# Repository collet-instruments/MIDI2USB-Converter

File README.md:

# 🎹 MIDI2USB Converter

<p align="center">

</p>

<p align="center">
  <strong>STM32F401-based USB MIDI converter supporting both MIDI 1.0 and MIDI 2.0 protocols.</strong>
</p>

## ✨ Features
- 🎵 **Dual Protocol Support**: MIDI 1.0 and MIDI 2.0 protocols
- 🔌 **USB Device Classes**: 
  - MIDI 1.0: Standard USB MIDI Class
  - MIDI 2.0: USB MIDI 2.0 Class with UMP support
- 🔄 **Dynamic Mode Switching**: Automatic detection based on SETUP switch
- 📦 **UMP (Universal MIDI Packet)**: Full support for MIDI 2.0 messaging
- 🔍 **MIDI-CI**: MIDI-CI v1.2 support
- 💡 **Visual Feedback**: LED status indicators
  - Red LED: USB MIDI 1.0 mode indicator
  - Blue LED: USB MIDI 2.0 mode indicator
- ⚡ **Real-time OS**: FreeRTOS-based multitasking
- 🔗 **UART Bridge**: Hardware TRS MIDI Type-A (3.5mm jack) interface support

## 📖 Usage

### Using USB MIDI1.0 Mode

- Switch SETUP (SW1) to MIDI1.0 and connect the USB Type-C port (J1) to a USB host
- The red LED (D5) will light up
- MIDI packets received at the MIDI IN port (J3) will be sent to the USB host
- Similarly, MIDI packets sent from the USB host will be output to the MIDI OUT port (J4)
- Data transfer status can be monitored via indicator LEDs (D2, D3) for both MIDI IN and MIDI OUT ports

### Using USB MIDI2.0 Mode

- Switch SETUP (SW1) to MIDI2.0 and connect the USB Type-C port (J1) to a USB host
- The blue LED (D6) will light up
- MIDI packets (MIDI1.0 byte stream) received at the MIDI IN port (J3) are converted to USB MIDI2.0 UMP (Universal MIDI Packet) and sent to the USB host
  - At this time, MIDI1.0 Voice Messages are extended to MIDI2.0 Protocol (UMP Message Type 4)
  - Similarly, MIDI2.0 UMP sent from the USB host is converted to MIDI1.0 byte stream and output to the MIDI OUT port (J4)
    - Since MIDI2.0 Protocol sent from the USB host is converted to MIDI1.0 Protocol, some data may be lost
- Data transfer status can be monitored via indicator LEDs (D2, D3) for both MIDI IN and MIDI OUT ports
- Some operating systems do not support USB MIDI2.0 drivers, in which case MIDI2.0 mode may not be available. Please use MIDI1.0 mode in such cases.

## 🔄 Protocol Conversion Rules

### MIDI 1.0 → MIDI 2.0 Conversion
The converter performs a 2-stage conversion process:
1. **Stage 1**: MIDI 1.0 byte stream → UMP (MIDI 1.0 Protocol)
2. **Stage 2**: UMP (MIDI 1.0 Protocol) → UMP (MIDI 2.0 Protocol)

**Key transformations**:
- **Resolution Enhancement**: 7-bit values are scaled up to 16-bit or 32-bit
  - Note velocity: 7-bit → 16-bit (e.g., 127 → ~65024)
  - Control Change values: 7-bit → 32-bit
  - Pitch Bend: 14-bit → 32-bit
- **Message Type**: Voice Messages are upgraded to UMP Message Type 4 (MIDI 2.0 Protocol)

### MIDI 2.0 → MIDI 1.0 Conversion
Direct conversion from UMP to MIDI 1.0 byte stream:

**Key transformations**:
- **Resolution Reduction**: High-resolution values are scaled down
  - Control values: 32-bit → 7-bit
- **Special handling for Note On velocity 0**:
  - In MIDI 2.0, Note On with velocity 0 remains a Note On
  - During conversion, velocity 0 is changed to 1 to prevent unintended Note Off behavior in MIDI 1.0
- **Data Loss**: MIDI 2.0-specific features (extended CC, per-note controllers) cannot be represented in MIDI 1.0

### Conversion Examples
- **MIDI 1.0 Note On**: `90 3C 64` (Ch1, Middle C, Velocity 100)
  → **MIDI 2.0 UMP**: `40902C00 32800000` (Velocity ≈ 51200)
  
- **MIDI 2.0 Note On**: Velocity 32768 (50% intensity)
  → **MIDI 1.0**: `90 3C 40` (Velocity 64, precision reduced)

## ⚠️ Caution

- The IN/OUT terminals of this product are **TRS MIDI Type-A only**. Do not use other types of cables.  
- Make sure not to confuse IN and OUT connections. Incorrect wiring may cause reverse current and damage your equipment.  
- This product is designed for **USB Type-C 5V power supply only**. Do not apply any other voltage.  
- The product may be damaged by static electricity. Please handle with proper ESD precautions.  
- Modifications or improper soldering may cause malfunction or accidents.  
- Do not use in environments with high temperature, high humidity, direct sunlight, or condensation.  
- Compatibility with all MIDI devices is **not guaranteed**.  

## 📜 Disclaimer

- This product is provided for **electronic hobby, educational, and research purposes**.  
- It is **not a consumer-ready product** and has **not been certified** under any safety standards or regulations (such as **PSE, Radio Act certification, CE, UL**, etc.).  
- By purchasing and using this product, you agree to the following terms:

### Use at Your Own Risk
- We accept no responsibility for any damage to equipment, personal injury, fire, data loss, or any other loss or accident resulting from the use of this product.

### Limitations of Use
- Do not use this product in industrial equipment, medical devices, safety systems, or any other applications where human life or property may be at risk.  
- Continuous long-term operation or use under heavy loads is not intended.

### Modification and Connections
- We are not responsible for any malfunction or damage caused by modification of this product or connection to unintended devices.

### Returns and Warranty
- If a manufacturing defect is confirmed, we will provide a replacement or refund.  
- No other warranties or guarantees are offered.

## ⚙️ Modification and Collaboration

- This product is provided as **open hardware**.  
  You are free to modify, reuse, or build upon the circuit and firmware.  
  However, **we cannot guarantee the operation or safety of modified versions**.  

- We welcome contributions from developers and users who wish to improve the design.  
  Please feel free to share feedback, modifications, or enhancement ideas.  

## 🛠️ Build Requirements

- ARM GCC toolchain (arm-none-eabi-gcc)
- CMake (3.22 or later)
- Ninja build system
- Git (for submodules)

## 📥 Getting Started

### Clone the Repository

```bash
git clone --recursive https://github.com/collet-instruments/MIDI2USB-Converter.git
cd MIDI2USB-Converter

# If you already cloned without --recursive, initialize submodules
git submodule init
git submodule update
```
### IDE Integration

**VS Code**: Use CMake extension for building and debugging with ST-Link.

- [STM32 VS Code extension](https://www.st.com/content/st_com/ja/campaigns/stm32-vs-code-extension-z11.html) makes setup easy.

## 🔨 Building

### Using CMake

```bash
# Configure the project
cmake --preset Debug

# Build the firmware
cmake --build --preset Debug

# The output files will be in build/Debug/
```
### Build Configurations

The project supports multiple build configurations:

- **Debug**: Development build with debug symbols (default)
- **Release**: Optimized build for production (-O2 optimization)
- **RelWithDebInfo**: Release build with debug info
- **MinSizeRel**: Size-optimized build (-Os optimization)

## 🧪 Testing

The project includes a comprehensive unit test suite using Unity framework.

### Running Tests

```bash
# Run all tests
cd test
make test

# Run specific test
make test-mode_manager

# Run tests with coverage
make clean
make COVERAGE=1
make test
```

## ✅ Code Quality

### Code Formatting

The project uses clang-format for code formatting. Configuration is in `.clang-format`.

```bash
# Format code
clang-format -i Core/Src/*.c Core/Inc/*.h

# Check formatting without modifying files
clang-format --dry-run --Werror Core/Src/*.c Core/Inc/*.h
```

### Static Analysis

```bash
# Run cppcheck
cppcheck --enable=warning,style,performance,portability \
  -I Core/Inc \
  Core/Src/
```

### CI/CD

GitHub Actions automatically runs on every push and pull request:

#### Workflows:
- **ci.yml**: Main CI pipeline
  - Builds STM32 firmware  
  - Runs all unit tests
  - Uploads firmware artifacts
  
- **code-quality.yml**: Code quality checks
  - Static analysis with cppcheck
  - Code formatting verification with clang-format
  
- **release.yml**: Automated releases
  - Triggers on version tags (v*)
  - Creates GitHub releases with firmware binaries

## 📁 Project Structure

```
├── Core/               # Application source code
├── Drivers/            # STM32 HAL and CMSIS drivers
├── submodules/         # External dependencies
│   ├── FreeRTOS-Kernel/
│   ├── tinyusb/
│   ├── AM_MIDI2.0Lib/
│   ├── tusb_ump/
│   └── Unity/
├── test/               # Unit tests (Unity framework)
│   ├── src/            # Test source files
│   ├── mock/           # Mock implementations
│   └── include/        # Test headers
├── ci/                 # CI/CD scripts
└── .github/            # CI/CD workflows
```

## 📦 Submodules

This project uses the following Git submodules:

| Submodule | Repository URL | Description |
|-----------|---------------|-------------|
| **FreeRTOS-Kernel** | https://github.com/FreeRTOS/FreeRTOS-Kernel.git | FreeRTOS kernel files only |
| **tinyusb** | https://github.com/hathach/tinyusb.git | An open source cross-platform USB stack for embedded system |
| **tusb_ump** | https://github.com/midi2-dev/tusb_ump | USB MIDI 2.0 tinyUSB Device driver with backwards compatibility to USB MIDI 1.0 |
| **AM_MIDI2.0Lib** | https://github.com/midi2-dev/AM_MIDI2.0Lib | A MIDI 2.0 C++ Library |
| **Unity** | https://github.com/ThrowTheSwitch/Unity.git | Simple unit testing for C |

## 🔧 Hardware

### 🎛️ Microcontroller
- **MCU**: STM32F401CBU6 (ARM Cortex-M4, 84MHz)
- **Flash**: 256KB
- **RAM**: 64KB

### 🔌 Interfaces
- **USB**: Full-Speed USB 2.0 (12Mbps)
- **UART**: MIDI serial interface (31.25 kbaud)
  - TX: PA2 (USART2_TX)
  - RX: PA3 (USART2_RX)
- **DEBUG**: ST-Link support (J2 connector)

### 📍 GPIO Pins
- **Mode Selection**: PA5 (SETUP pin)
  - High: USB MIDI 2.0 mode
  - Low: USB MIDI 1.0 mode
- **LEDs**:
  - M1LED: PA4 - USB MIDI 1.0 mode indicator
  - M2LED: PA6 - USB MIDI 2.0 mode indicator

### ⚡ Power
- Powered via USB (5V)
- 3.3V internal operation

## 💻 Development

### Running Tests Locally
```bash
# Quick test before pushing
./ci/test-ci-locally.sh

# Install optional CI tools
./ci/install-ci-tools.sh
```

### Debugging

1. **VS Code**: Use CMake extension and ST-Link for debugging
2. **OpenOCD**: Manual debugging with GDB

- Connect the J2 connector (NRST, SYS_SWCLK, SYS_SWDIO) to ST-Link for debugging. USART1 is also available for printf debugging.

## 🤝 Contributing

We welcome contributions! Please see [CONTRIBUTING.md](CONTRIBUTING.md) for details on:
- How to submit issues
- How to submit pull requests
- Code style guidelines
- Development setup

## 📜 Code of Conduct

This project adheres to a Code of Conduct. By participating, you are expected to uphold this code. Please see [CODE_OF_CONDUCT.md](CODE_OF_CONDUCT.md) for details.

## 📄 License

This project is licensed under the MIT License - see the [LICENSE](LICENSE) file for details.

**Hardware Design**: All hardware design files including schematics, PCB layouts, and manufacturing files in the `hardware/` directory are also covered under the same MIT License.

### Third-party Licenses

This project uses the following open-source libraries:
- **FreeRTOS-Kernel**: MIT License
- **TinyUSB**: MIT License
- **AM_MIDI2.0Lib**: MIT License
- **Unity Test Framework**: MIT License
- **STM32 HAL Drivers**: BSD 3-Clause License (STMicroelectronics)

## 👥 Authors and Acknowledgments

- USB MIDI 2.0 implementation based on TinyUSB and AM_MIDI2.0Lib
- STM32 HAL drivers by STMicroelectronics
- Special thanks to all contributors

## 💬 Support

For questions and support:
- Open an issue on GitHub
- Check existing issues and discussions
- See documentation in the repository

## 📝 Copyright

Copyright © 2025 Collet Instruments. All rights reserved.

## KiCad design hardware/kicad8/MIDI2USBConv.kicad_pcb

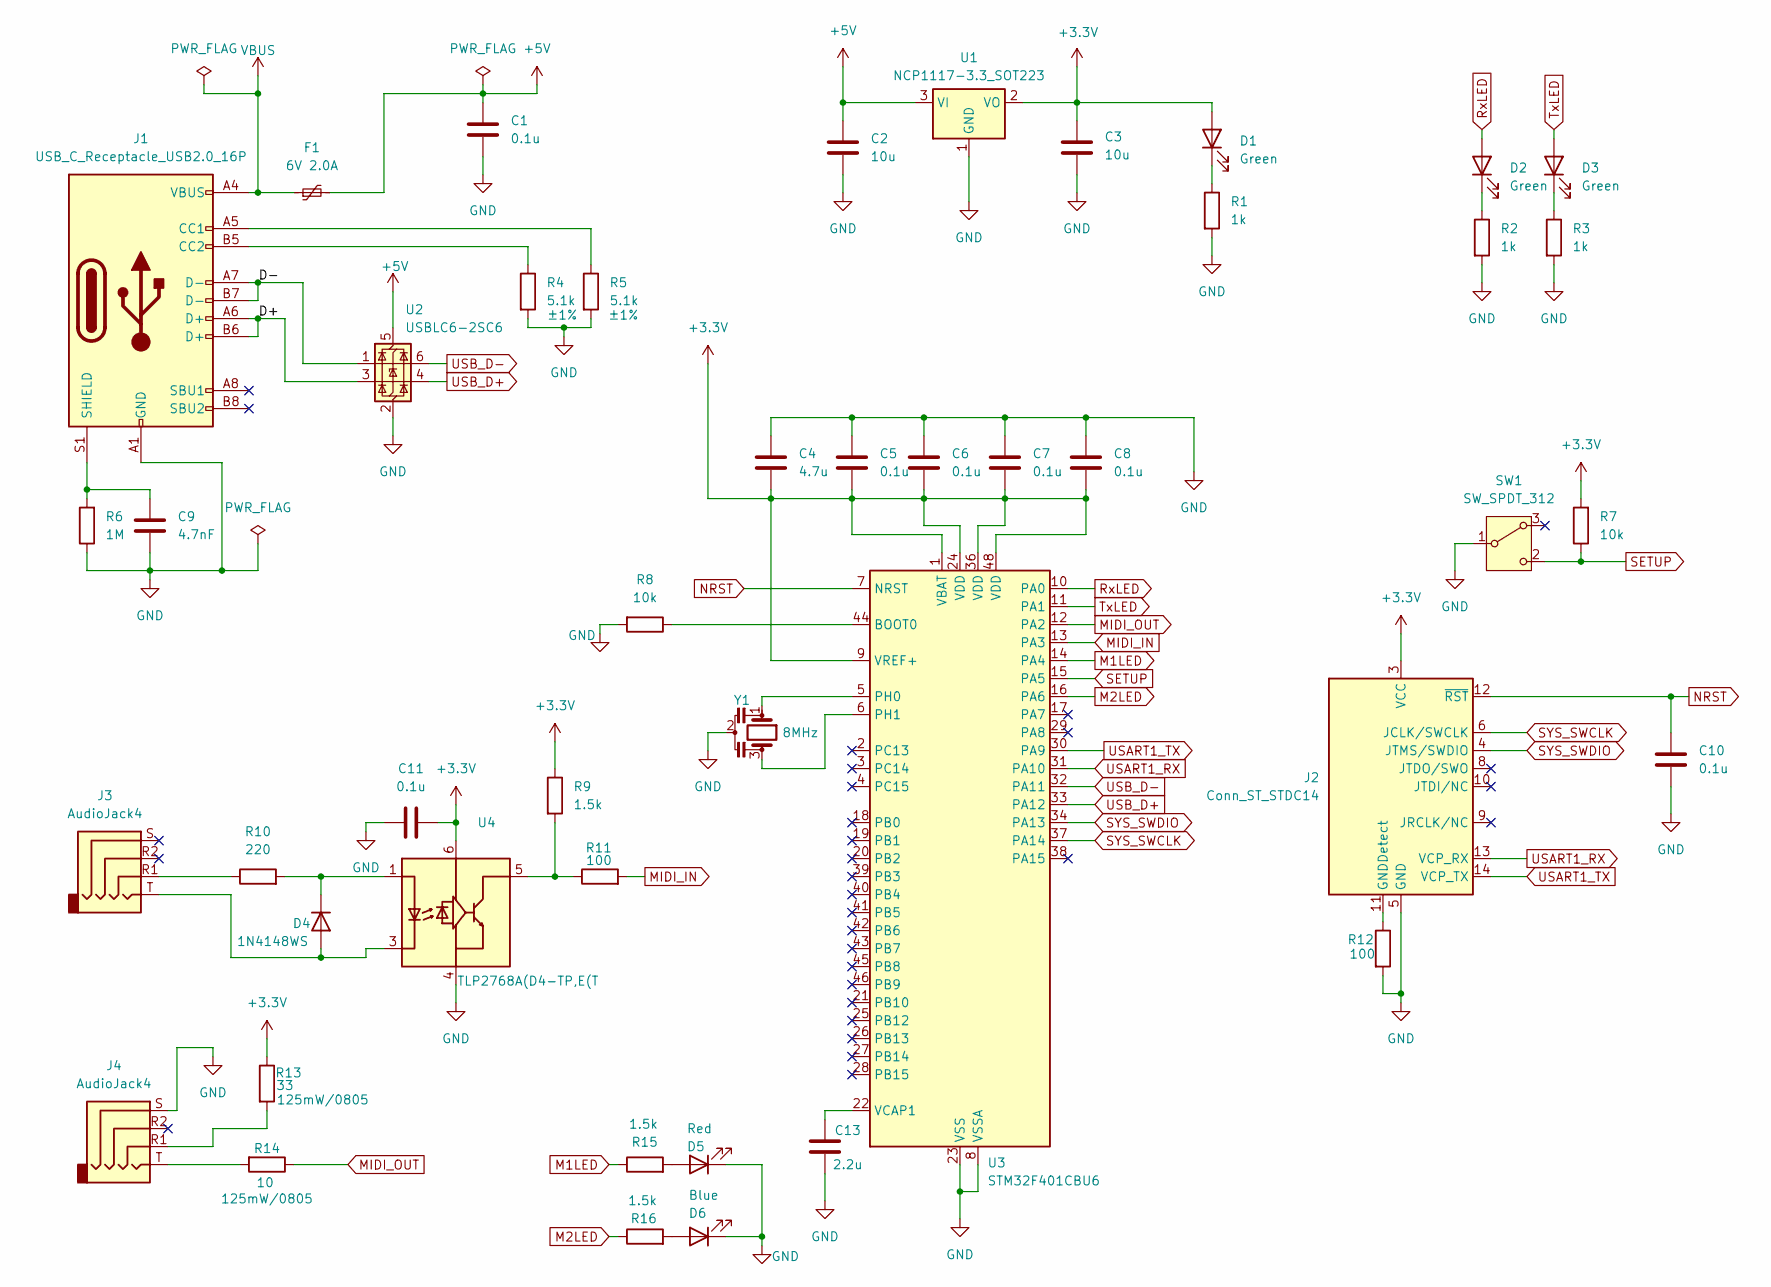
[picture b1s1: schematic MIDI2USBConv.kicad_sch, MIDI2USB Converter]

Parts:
C1, C5, C6, C7, C8, C10, C11: 0.1u; C_0402_1005Metric; LCSC C1525
C2, C3: 10u; C_0603_1608Metric; LCSC C1691
C4: 4.7u; C_0603_1608Metric; LCSC C1705
C9: 4.7nF; C_0402_1005Metric; LCSC C1538
C13: 2.2u; C_0603_1608Metric; LCSC C1607
D1, D2, D3: Green; LED_0402_1005Metric; LCSC C434449
D4: 1N4148WS; D_SOD-323; LCSC C2128
D5: Red; LED_0402_1005Metric; LCSC C264407
D6: Blue; LED_0402_1005Metric; LCSC C131223
F1: 6V 2.0A; Fuse_1206_3216Metric; LCSC C20803
J1: USB_C_Receptacle_USB2.0_16P; USB_C_Receptacle_G-Switch_GT-USB-7010ASV; LCSC C2988369
J2: Conn_ST_STDC14; STDC14_SMD; LCSC C42455944
J3, J4: AudioJack4; Jack_3.5mm_PJ320D_Horizontal; LCSC C95562
R1, R2, R3: 1k; R_0402_1005Metric; LCSC C11702
R4, R5: 5.1k; R_0402_1005Metric; LCSC C25905
R6: 1M; R_0402_1005Metric; LCSC C26083
R7, R8: 10k; R_0402_1005Metric; LCSC C25531
R9, R15, R16: 1.5k; R_0402_1005Metric; LCSC C25867
R10: 220; R_0402_1005Metric; LCSC C25091
R11, R12: 100; R_0402_1005Metric; LCSC C25076
R13: 33; R_0805_2012Metric; LCSC C17634
R14: 10; R_0805_2012Metric; LCSC C17415
SW1: SW_SPDT_312; SW_SPDT_PCM12; LCSC C221841
U1: NCP1117-3.3_SOT223; SOT-223-3_TabPin2; LCSC C26537
U2: USBLC6-2SC6; SOT-23-6; LCSC C5310974
U3: STM32F401CBU6; QFN-48-1EP_7x7mm_P0.5mm_EP5.6x5.6mm; LCSC C118825
U4: TLP2768A(D4-TP,E(T; SO-6L_10x3.84mm_P1.27mm; LCSC C5370532
Y1: 8MHz; Resonator_SMD_Murata_CSTxExxV-3Pin_3.0x1.1mm; LCSC C341524

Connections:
+3.3V: C3.1, C4.2, C5.2, C6.2, C7.2, C8.2, C11.2, D1.2 (A), J2.3 (VCC), R7.2, R9.1, R13.1, U1.2 (VO), U3.1 (VBAT), U3.9 (VREF+), U3.24 (VDD), U3.36 (VDD), U3.48 (VDD), U4.6 (VDD)
+5V: C1.1, C2.1, F1.2, U1.3 (VI), U2.5 (VBUS)
/D+: J1.A6 (D+), J1.B6 (D+), U2.3 (I/O2)
/D-: J1.A7 (D-), J1.B7 (D-), U2.1 (I/O1)
GND: C1.2, C2.2, C3.2, C4.1, C5.1, C6.1, C7.1, C8.1, C9.1, C10.2, C11.1, C13.2, D5.1 (K), D6.1 (K), J1.A1 (GND), J1.A12 (GND), J1.B1 (GND), J1.B12 (GND), J2.5 (GND), J2.7 (GND), J4.S, R1.2, R2.2, R3.2, R4.2, R5.2, R6.1, R8.2, R12.2, SW1.1 (B), U1.1 (GND), U2.2 (GND), U3.8 (VSSA), U3.23 (VSS), U3.35 (VSS), U3.47 (VSS), U3.49 (VSS), U4.4 (GND), Y1.2
M1LED: R15.1, U3.14 (PA4)
M2LED: R16.1, U3.16 (PA6)
MIDI_IN: R11.2, U3.13 (PA3)
MIDI_OUT: R14.1, U3.12 (PA2)
NRST: C10.1, J2.12 (~RST), U3.7 (NRST)
unnamed: D1.1 (K), R1.1
unnamed: D2.1 (K), R2.1
unnamed: D3.1 (K), R3.1
unnamed: D4.2 (A), J3.T, U4.3 (K)
unnamed: D4.1 (K), R10.2, U4.1 (A)
unnamed: D5.2 (A), R15.2
unnamed: D6.2 (A), R16.2
unnamed: J1.A5 (CC1), R5.1
unnamed: J1.B5 (CC2), R4.1
unnamed: C9.2, J1.S1 (SHIELD), R6.2
unnamed: J2.11 (GNDDetect), R12.1
unnamed: J3.R1, R10.1
unnamed: J4.R1, R13.2
unnamed: J4.T, R14.2
unnamed: R8.1, U3.44 (BOOT0)
unnamed: U3.5 (PH0), Y1.1
unnamed: U3.6 (PH1), Y1.3
unnamed: C13.1, U3.22 (VCAP1)
unnamed: R9.2, R11.1, U4.5 (VO)
RxLED: D2.2 (A), U3.10 (PA0)
SETUP: R7.1, SW1.2 (C), U3.15 (PA5)
SYS_SWCLK: J2.6 (JCLK/SWCLK), U3.37 (PA14)
SYS_SWDIO: J2.4 (JTMS/SWDIO), U3.34 (PA13)
TxLED: D3.2 (A), U3.11 (PA1)
USART1_RX: J2.13 (VCP_RX), U3.31 (PA10)
USART1_TX: J2.14 (VCP_TX), U3.30 (PA9)
USB_D+: U2.4 (I/O2), U3.33 (PA12)
USB_D-: U2.6 (I/O1), U3.32 (PA11)
VBUS: F1.1, J1.A4 (VBUS), J1.A9 (VBUS), J1.B4 (VBUS), J1.B9 (VBUS)

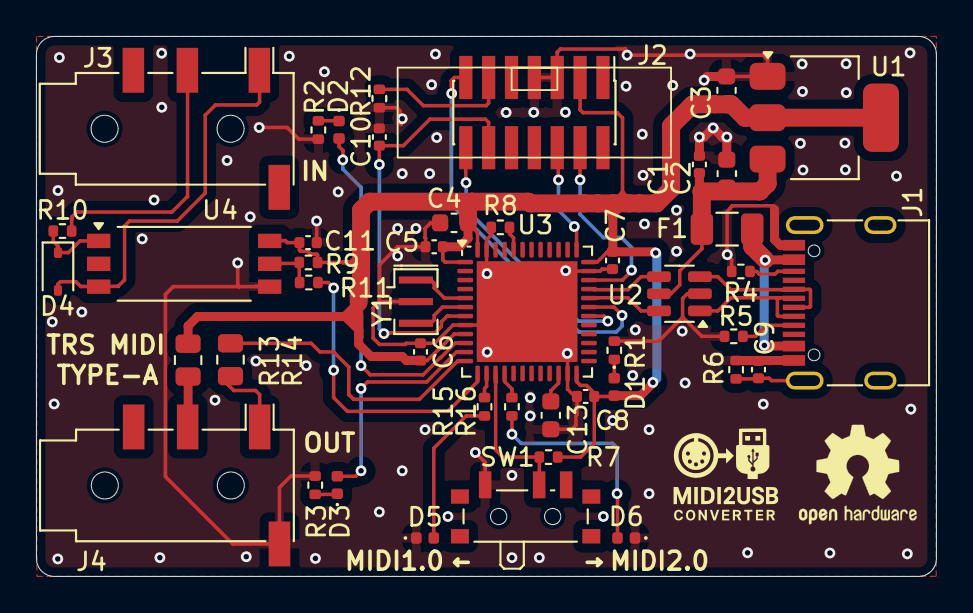
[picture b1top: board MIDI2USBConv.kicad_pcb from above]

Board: 2 copper layers, 50.0 x 30.0 mm, 45 parts (0 on the bottom side), 39 nets.

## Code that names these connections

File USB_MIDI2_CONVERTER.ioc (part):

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Mcu.Name=STM32F401C(B-C)Ux
Mcu.Package=UFQFPN48
Mcu.UserName=STM32F401CBUx
PA0-WKUP.GPIOParameters=GPIO_Label
PA0-WKUP.GPIO_Label=RxMIDI
PA0-WKUP.Signal=GPIO_Output
PA1.GPIOParameters=GPIO_Label
PA1.GPIO_Label=TxMIDI
PA1.Signal=GPIO_Output
PA10.Mode=Asynchronous
PA10.Signal=USART1_RX
PA11.Mode=Device_Only
PA11.Signal=USB_OTG_FS_DM
PA12.Mode=Device_Only
PA12.Signal=USB_OTG_FS_DP
PA13.Mode=Serial_Wire
PA13.Signal=SYS_JTMS-SWDIO
PA14.Mode=Serial_Wire
PA14.Signal=SYS_JTCK-SWCLK
PA2.GPIOParameters=GPIO_Label
PA2.GPIO_Label=MIDI_OUT
PA2.Mode=Asynchronous
PA2.Signal=USART2_TX
PA3.GPIOParameters=GPIO_Label
PA3.GPIO_Label=MIDI_IN
PA3.Mode=Asynchronous
PA3.Signal=USART2_RX
PA4.GPIOParameters=GPIO_Label
PA4.GPIO_Label=M1LED
PA4.Signal=GPIO_Output
PA5.GPIOParameters=GPIO_PuPd,GPIO_Label
PA5.GPIO_Label=SETUP
PA5.GPIO_PuPd=GPIO_NOPULL
PA5.Signal=GPIO_Input
PA6.GPIOParameters=GPIO_Label
PA6.GPIO_Label=M2LED
PA6.Signal=GPIO_Output
PA9.Mode=Asynchronous
PA9.Signal=USART1_TX
PH0\ -\ OSC_IN.Mode=HSE-External-Oscillator
PH0\ -\ OSC_IN.Signal=RCC_OSC_IN
PH1\ -\ OSC_OUT.Mode=HSE-External-Oscillator
PH1\ -\ OSC_OUT.Signal=RCC_OSC_OUT
RCC.HSE_VALUE=8000000
RCC.SYSCLKFreq_VALUE=84000000
RCC.SYSCLKSource=RCC_SYSCLKSOURCE_PLLCLK
board=custom

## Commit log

2025-08-20 Add submodules for FreeRTOS, tinyusb, tusb_ump, AM_MIDI2.0Lib, and Unity
2025-08-20 Add project files and CI/CD setup
2025-08-20 test: clean up obsolete test files and build rules
    - Remove test_midi_parser.c (caused link errors with MIDI_GetExpectedLength)
    - Remove test_ump_wordcount.c (stub no longer needed)
    - Remove unused test_usb_descriptors build rule from Makefile
    - Keep only actively used test files
2025-08-20 Bump softprops/action-gh-release from 1 to 2
    Bumps [softprops/action-gh-release](https://github.com/softprops/action-gh-release) from 1 to 2.
    - [Release notes](https://github.com/softprops/action-gh-release/releases)
    - [Changelog](https://github.com/softprops/action-gh-release/blob/master/CHANGELOG.md)
    - [Commits](https://github.com/softprops/action-gh-release/compare/v1...v2)
    ---
    updated-dependencies:
2025-08-20 Bump actions/checkout from 4 to 5
    Bumps [actions/checkout](https://github.com/actions/checkout) from 4 to 5.
    - [Release notes](https://github.com/actions/checkout/releases)
    - [Changelog](https://github.com/actions/checkout/blob/main/CHANGELOG.md)
    - [Commits](https://github.com/actions/checkout/compare/v4...v5)
    ---
    updated-dependencies:
2025-08-26 fix: correct MIDI endpoint addresses in USB configuration descriptor
2025-08-26 fix: update language ID in USB string descriptor to English (0x0409)
2025-08-26 fix: update endpoint name and product instance ID for clarity
2025-08-26 fix: update USB interface string definitions and remove obsolete tests
2025-09-12 Implement code changes to enhance functionality and improve performance
2025-09-12 fix: wrap images in usage section with paragraph tags for better formatting
2025-09-18 fix: implement MIDI filtering at conversion and transmission stages
2025-09-24 fix: update USB Vendor and Product IDs to values awaiting OpenMoko assignment
2025-09-24 feat: add versioning support with extraction and storage in firmware
2025-10-27 build(deps): bump actions/upload-artifact from 4 to 5
    Bumps [actions/upload-artifact](https://github.com/actions/upload-artifact) from 4 to 5.
    - [Release notes](https://github.com/actions/upload-artifact/releases)
    - [Commits](https://github.com/actions/upload-artifact/compare/v4...v5)
    ---
    updated-dependencies:
    - dependency-name: actions/upload-artifact
2025-11-24 build(deps): bump actions/checkout from 5 to 6
    Bumps [actions/checkout](https://github.com/actions/checkout) from 5 to 6.
    - [Release notes](https://github.com/actions/checkout/releases)
    - [Changelog](https://github.com/actions/checkout/blob/main/CHANGELOG.md)
    - [Commits](https://github.com/actions/checkout/compare/v5...v6)
    ---
    updated-dependencies:
2025-12-15 build(deps): bump actions/upload-artifact from 5 to 6
    Bumps [actions/upload-artifact](https://github.com/actions/upload-artifact) from 5 to 6.
    - [Release notes](https://github.com/actions/upload-artifact/releases)
    - [Commits](https://github.com/actions/upload-artifact/compare/v5...v6)
    ---
    updated-dependencies:
    - dependency-name: actions/upload-artifact
2026-03-02 build(deps): bump actions/upload-artifact from 5 to 7
    Bumps [actions/upload-artifact](https://github.com/actions/upload-artifact) from 5 to 7.
    - [Release notes](https://github.com/actions/upload-artifact/releases)
    - [Commits](https://github.com/actions/upload-artifact/compare/v5...v7)
    ---
    updated-dependencies:
    - dependency-name: actions/upload-artifact

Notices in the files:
hardware/kicad8/MIDI2USBConv.kicad_sch:
Copyright (c) 2025 Collet Instruments
License: MIT License
